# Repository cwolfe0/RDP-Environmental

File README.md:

# RDP-Environmental
This is a PCB designed in KiCad for the UAH SHC HELEN project's Radiation Detection Payload (RDP). This board is intended to gather environmental inupt including temperature, pressure and GPS.  This information is processed and saved and potentially shared with an external FPGA.

The rendering above is a rough idea of what this payload will look like with some of its components installed.

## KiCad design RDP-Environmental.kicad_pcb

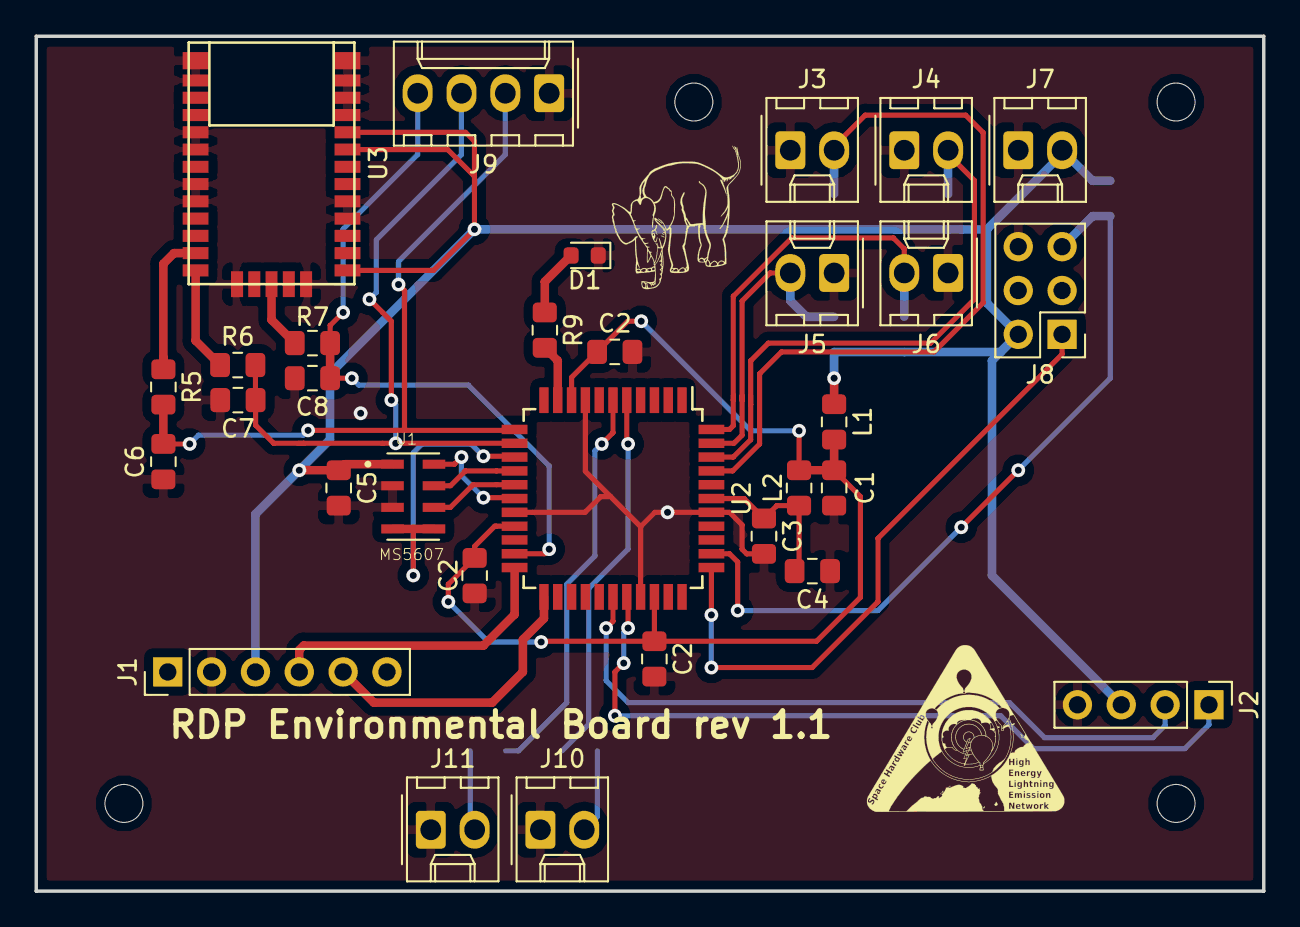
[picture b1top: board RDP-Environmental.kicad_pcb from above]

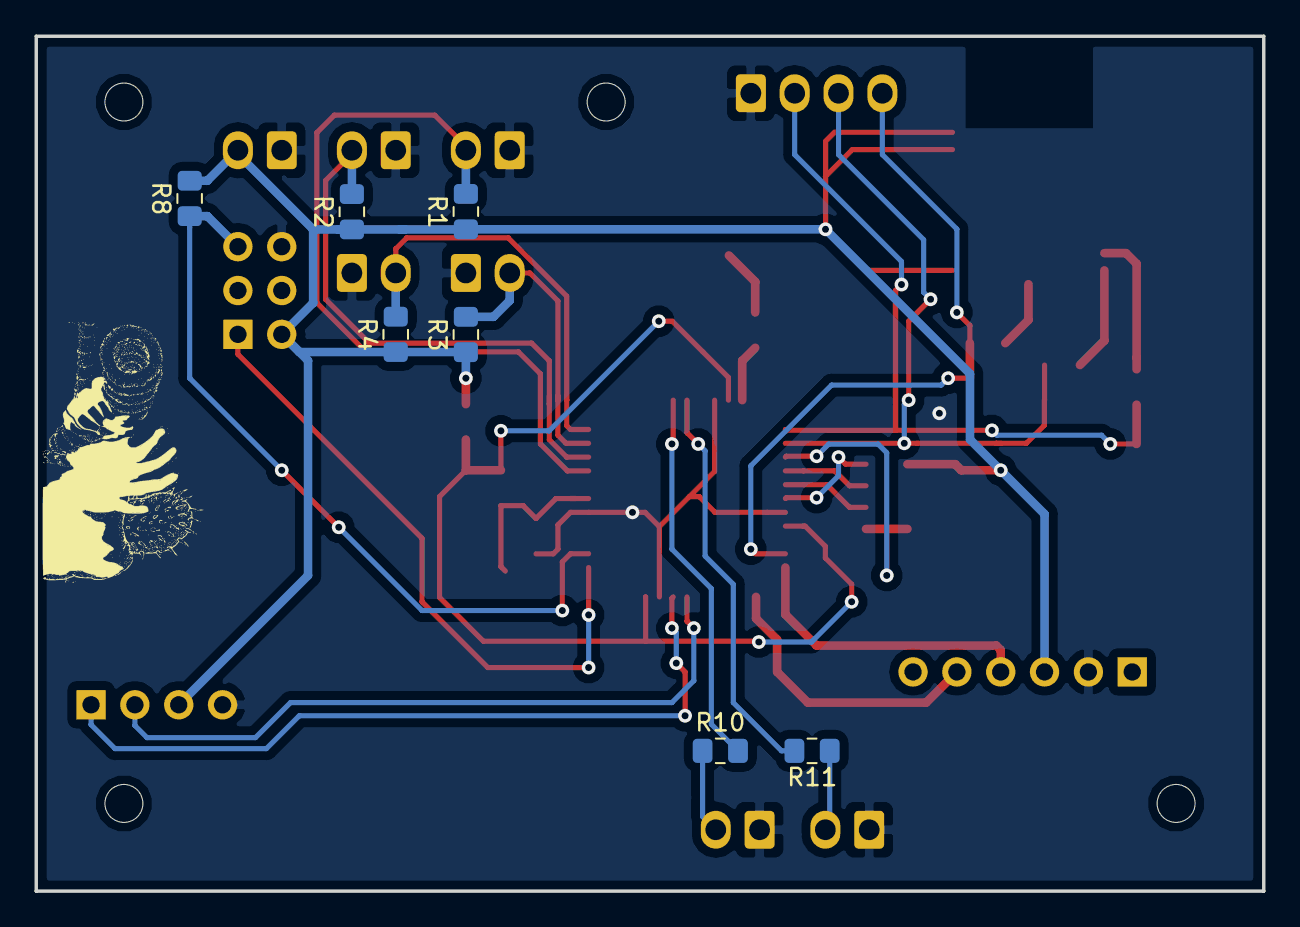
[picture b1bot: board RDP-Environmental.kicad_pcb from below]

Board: 2 copper layers, 71.1 x 49.5 mm, 38 parts (7 on the bottom side), 30 nets.

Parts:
C1, C4: 10μF; C_0805_2012Metric_Pad1.15x1.40mm_HandSolder
C2, C2#2, C2#3, C3, C5: 100nF; C_0805_2012Metric_Pad1.15x1.40mm_HandSolder
C6, C7, C8: C_Small; C_0805_2012Metric_Pad1.15x1.40mm_HandSolder
D1: LED; LED_0603_1608Metric
J1: OPENLOG; PinHeader_1x06_P2.54mm_Vertical
J2: MPU; PinHeader_1x04_P2.54mm_Vertical
J3: RT1; Molex_KK-254_AE-6410-02A_1x02_P2.54mm_Vertical
J4: RT2; Molex_KK-254_AE-6410-02A_1x02_P2.54mm_Vertical
J5: RT3; Molex_KK-254_AE-6410-02A_1x02_P2.54mm_Vertical
J6: RT4; Molex_KK-254_AE-6410-02A_1x02_P2.54mm_Vertical
J7: 3.3V; Molex_KK-254_AE-6410-02A_1x02_P2.54mm_Vertical
J8: AVR-PDI-6; PinHeader_2x03_P2.54mm_Vertical
J9: FPGAO; Molex_KK-254_AE-6410-04A_1x04_P2.54mm_Vertical
J10: Environmental; Molex_KK-254_AE-6410-02A_1x02_P2.54mm_Vertical
J11: GPS; Molex_KK-254_AE-6410-02A_1x02_P2.54mm_Vertical
L1: 10μH; L_0805_2012Metric_Pad1.15x1.40mm_HandSolder
L2: FB; L_0805_2012Metric_Pad1.15x1.40mm_HandSolder
R1, R2, R3, R4: 50kΩ; R_0805_2012Metric_Pad1.15x1.40mm_HandSolder
R5, R6, R7, R9: 220Ω; R_0805_2012Metric_Pad1.15x1.40mm_HandSolder
R8: 10kΩ; R_0805_2012Metric_Pad1.15x1.40mm_HandSolder
R10, R11: R_Small_US; R_0805_2012Metric_Pad1.15x1.40mm_HandSolder
U1: MS5607; SON125P300X500X100-8N
U2: ATxmega32A4U-AU; TQFP-44_10x10mm_P0.8mm
U3: CAM-M8Q-0; CAM-M8

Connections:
+3V3: C5.1, J1.3, J2.3, J7.2, J8.2, L1.1, R1.1, R2.1, R3.1, R4.1, R8.2, U1.1, U3.1, U3.8, U3.9
/ENV_STAT: J10.2, R10.1
/GPS_STAT: J11.2, R11.2
/LED: R9.2, U2.10
/MISOC: U1.6, U2.16
/MOSIC: U1.7, U2.15
/PDI-CLK: J8.5, R8.1, U2.35
/PDI-DATA: J8.1, U2.34
/PPS: C8.1, J9.4, R7.1, U2.21
/RT1: J3.2, R1.2, U2.41
/RT2: J4.2, R2.2, U2.42
/RT3: J5.2, R3.2, U2.43
/RT4: J6.2, R4.2, U2.44
/RXC: C6.2, J9.2, R5.2, U2.12
/RXD: J1.4, U2.22
/SCLE: J2.1, U2.29
/SCLKC: U1.8, U2.17
/SDAD: J2.2, U2.28
/SSC: U1.4, U1.5, U2.14
/TXC: C7.1, J9.3, R6.2, U2.13
/TXD: J1.5, U2.23
GND: C1.2, C2.2, C2#2.2, C2#3.2, C3.2, C4.1, C5.2, C6.1, C7.2, C8.2, D1.1, J1.2, J2.4, J3.1, J4.1, J5.1, J6.1, J7.1, J8.6, J9.1, J10.1, J11.1, U1.2, U1.3, U2.8, U2.18, U2.30, U2.38, U3.4, U3.5, U3.10, U3.11, U3.12, U3.13, U3.14, U3.15, U3.18, U3.19, U3.21, U3.22, U3.27, U3.31
unnamed: C1.1, C2.1, C2#2.1, C2#3.1, L1.2, L2.1, U2.9, U2.19, U2.31
unnamed: C3.1, C4.2, L2.2, U2.39
unnamed: D1.2, R9.1
unnamed: R5.1, U3.25
unnamed: R6.1, U3.26
unnamed: R7.2, U3.29
unnamed: R10.2, U2.5
unnamed: R11.1, U2.6

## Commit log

2018-10-29 Touch up readme
2018-10-29 Fix render
2018-10-29 Fix Rendering
2018-10-30 Add GPS and groud to output for FPGA
2018-11-01 Add dimensions to PCB CAD
2018-11-03 Fix MPU 9250 clearance
2018-11-05 Fix thermistor resistance values
2019-01-10 Fix drill files in GBR/Gerbers.zip. Increment rev number
2019-01-10 Update render
2019-02-02 Add status LED pins for GPS and general status
2019-02-04 Make holes bigger
